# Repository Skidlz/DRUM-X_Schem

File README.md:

# DRUM-X_Schem
Schematics for the Pearl DRUM-X

These schematic are based off of the control section and one voice from the Pearl DRUM-X. 

The board layout is compromised for the sake of the schematic; The SIP resistors have been replace with discrete resistors.

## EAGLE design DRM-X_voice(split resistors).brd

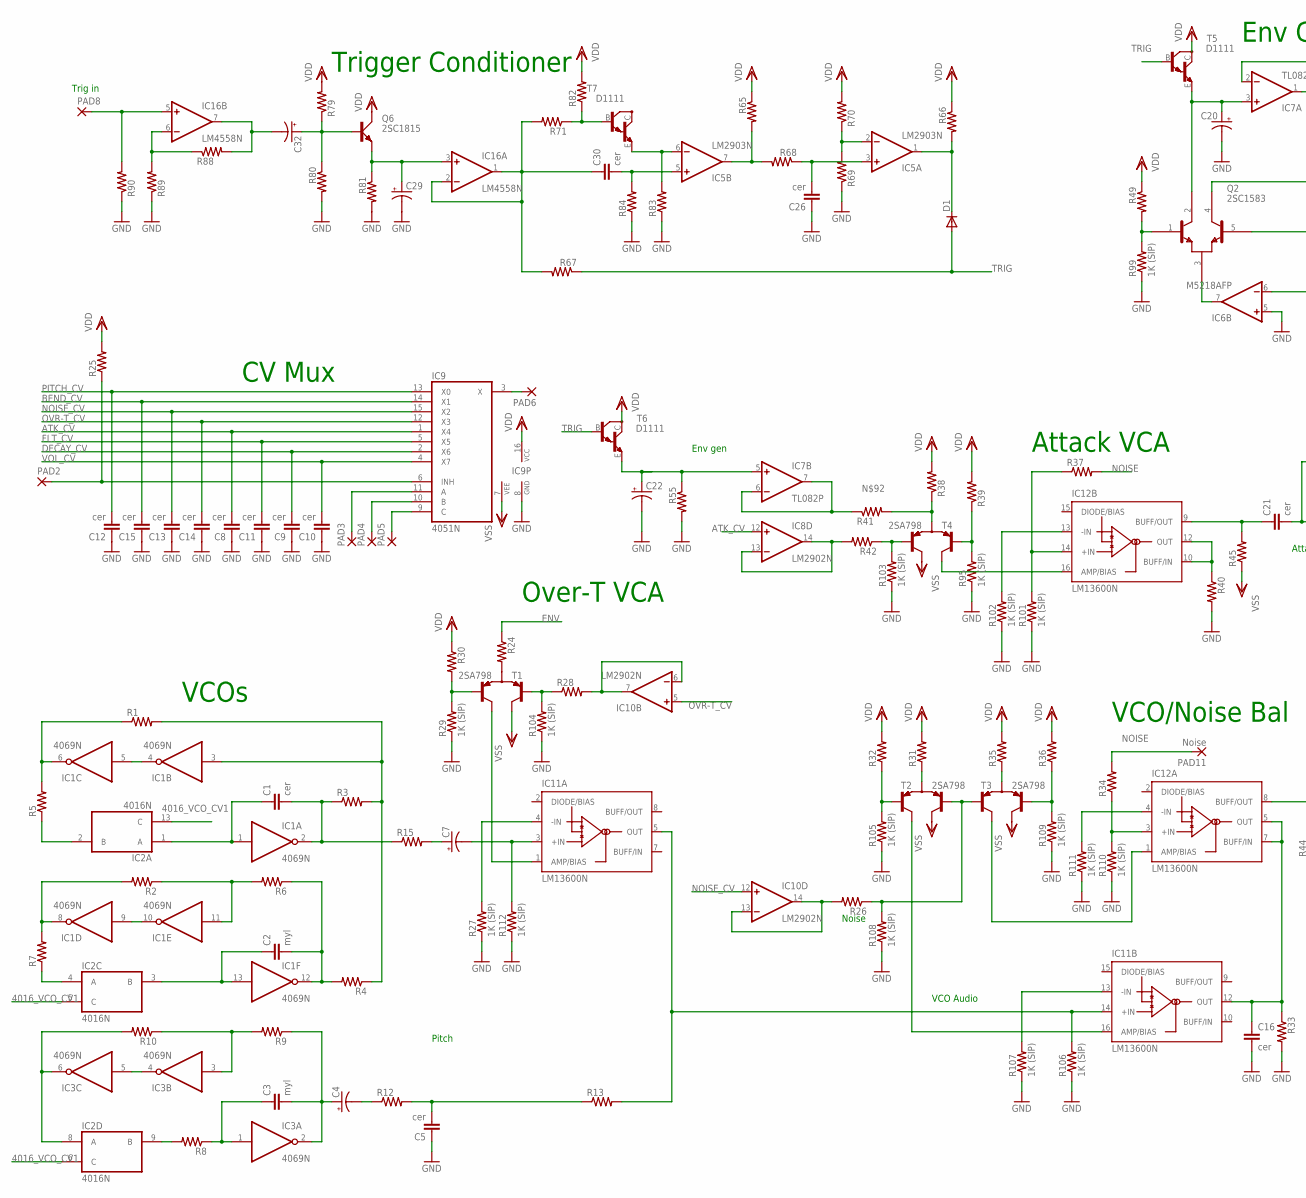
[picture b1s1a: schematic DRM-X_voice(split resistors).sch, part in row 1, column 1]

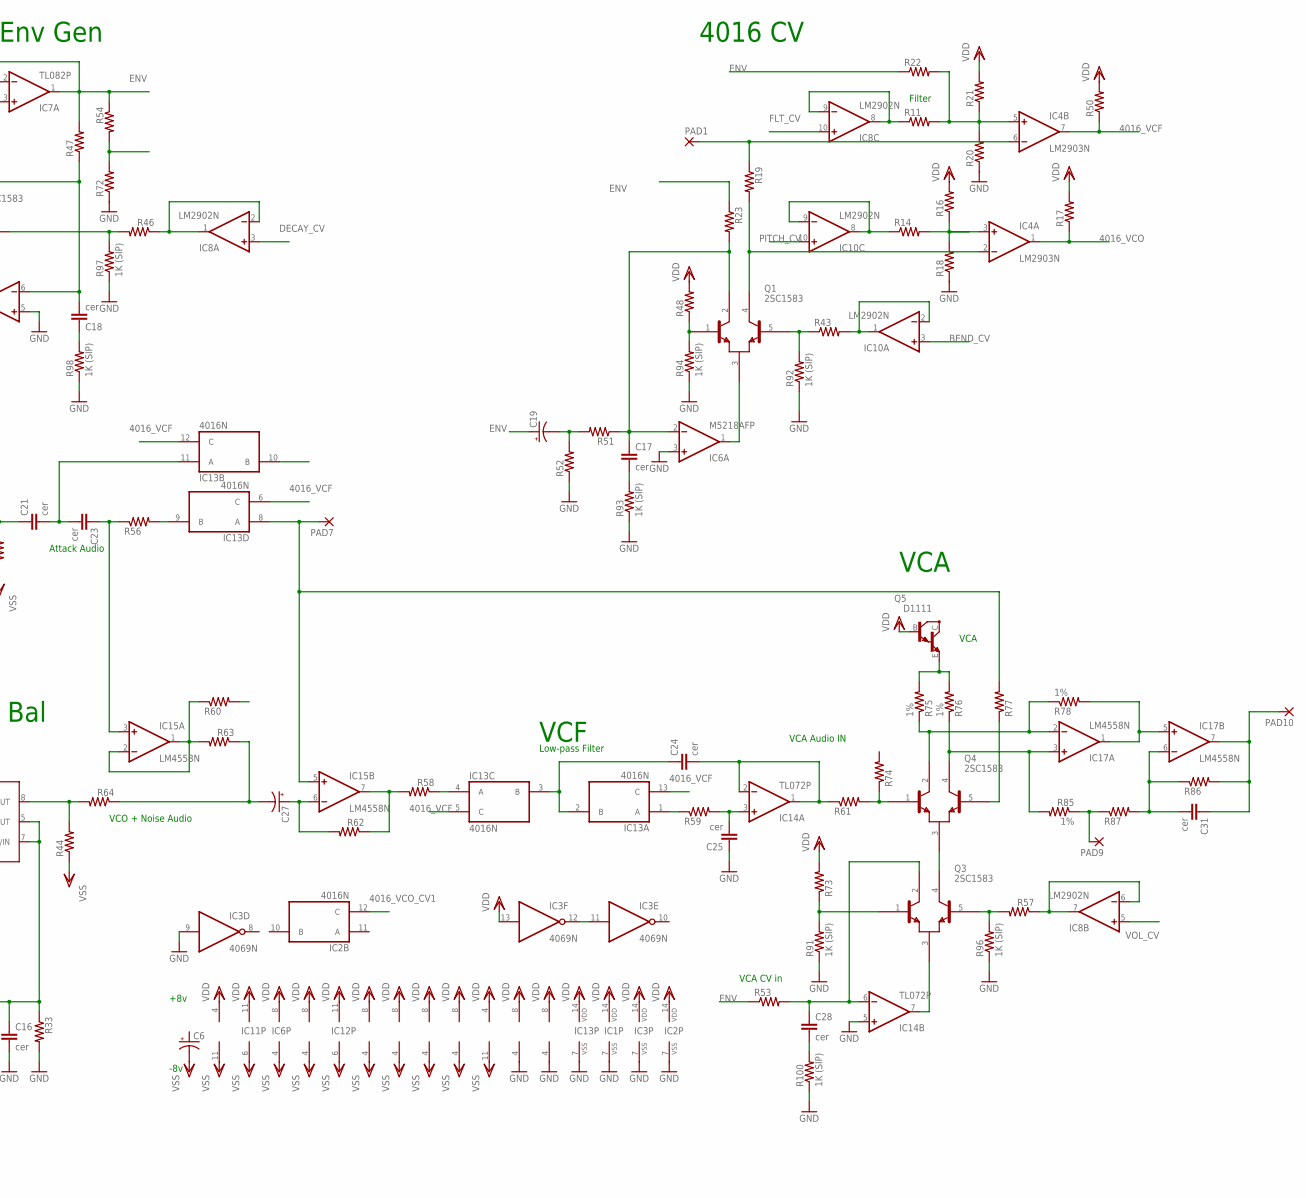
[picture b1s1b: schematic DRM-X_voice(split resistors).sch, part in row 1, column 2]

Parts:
C1, C5, C8, C9, C10, C11, C12, C13, C14, C15, C16, C17, C18, C21, C23, C24, C25, C26, C28, C30, C31: cer; C025-025X050
C2, C3: myl; C025-024X044
C4, C7, C19, C20, C22, C27, C29, C32: CPOL-USE2.5-5; E2,5-5
C6: CPOL-USE2.5-7; E2,5-7
D1: DIODE-D-5; D-5
IC1, IC3: 4069N; DIL14
IC2, IC13: 4016N; DIL14
IC4, IC5: LM2903N; DIL08
IC6: M5218AFP; SOP8
IC7: TL082P; DIL08
IC8, IC10: LM2902N; DIL14
IC9: 4051N; DIL16
IC11, IC12: LM13600N; DIL16
IC14: TL072P; DIL08
IC15, IC16, IC17: LM4558N; DIL08
PAD1, PAD2, PAD3, PAD4, PAD5, PAD6, PAD7, PAD8, PAD9, PAD10: 2,0/0,9-O
PAD11: Noise; 2,0/0,9-O
Q1, Q2, Q3, Q4: 2SC1583; XSIST_SIP5
Q5: D1111; TO92-ECB
Q6: 2SC1815; TO92-LINE
R1, R2, R3, R4, R5, R6, R7, R8, R9, R10, R11, R12, R13, R14, R15, R16, R17, R18, R19, R20, R21, R22, R23, R24, R25, R26, R28, R30, R31, R32, R33, R34, R35, R36, R37, R38, R39, R40, R41, R42, R43, R44, R45, R46, R47, R48, R49, R50, R51, R52, R53, R54, R55, R56, R57, R58, R59, R60, R61, R62, R63, R64, R65, R66, R67, R68, R69, R70, R71, R72, R73, R74, R77, R79, R80, R81, R82, R83, R84, R86, R87, R88, R89, R90: R-US_0204/7; 0204/7
R27, R29, R91, R92, R93, R94, R95, R96, R97, R98, R99, R100, R101, R102, R103, R104, R105, R106, R107, R108, R109, R110, R111, R112: 1K (SIP); 0204/7
R75, R76, R78, R85: 1%; 0204/7
T1, T2, T3, T4: 2SA798; SIP-5
T5, T6, T7: D1111; TO92-ECB

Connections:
4016_VCF: IC4.7 (OUT), IC13.5 (C), IC13.6 (C), IC13.12 (C), IC13.13 (C), R50.1
4016_VCO: IC4.1 (OUT), R17.1
4016_VCO_CV1: IC2.5 (C), IC2.6 (C), IC2.12 (C), IC2.13 (C)
ATK_CV: C8.2, IC8.12 (+IN), IC9.1 (X4)
BEND_CV: C15.2, IC9.14 (X1), IC10.3 (+IN)
DECAY_CV: C9.2, IC8.3 (+IN), IC9.2 (X6)
ENV: C19.+, IC7.1 (OUT), IC7.2 (-IN), R22.1, R23.1, R24.1, R47.2, R53.1, R54.1
FLT_CV: C11.2, IC8.10 (+IN), IC9.5 (X5)
GND: C5.1, C8.1, C9.1, C10.1, C11.1, C12.1, C13.1, C14.1, C15.1, C16.2, C20.-, C22.-, C25.1, C26.1, C29.-, IC1.7 (VSS), IC2.7 (VSS), IC3.7 (VSS), IC3.9 (I), IC4.4 (V-), IC5.4 (V-), IC6.3 (+IN), IC6.5 (+IN), IC9.8 (GND), IC13.7 (VSS), IC14.5 (+IN), R18.1, R20.1, R27.1, R29.1, R33.2, R40.2, R52.1, R55.2, R69.1, R72.1, R80.2, R81.2, R83.1, R84.1, R89.1, R90.1, R91.1, R92.1, R93.1, R94.1, R95.1, R96.1, R97.1, R98.1, R99.1, R100.1, R101.1, R102.1, R103.1, R104.1, R105.1, R106.1, R107.1, R108.1, R109.1, R110.1, R111.1, R112.1
unnamed: IC1.4 (O), IC1.5 (I)
unnamed: IC1.6 (O), R1.1, R5.2
unnamed: C1.1, IC1.1 (I), IC2.1 (A)
unnamed: C1.2, IC1.2 (O), R3.1, R15.1
unnamed: IC1.8 (O), R2.2, R7.2
unnamed: IC1.11 (I), R2.1, R6.2
unnamed: IC1.3 (I), R1.2, R3.2, R4.1
unnamed: IC2.4 (A), R7.1
unnamed: IC1.9 (I), IC1.10 (O)
unnamed: C2.1, IC1.13 (I), IC2.3 (B)
unnamed: C2.2, IC1.12 (O), R4.2, R6.1
unnamed: C3.2, C4.+, IC3.2 (O), R9.1
unnamed: C3.1, IC3.1 (I), R8.1
unnamed: C28.1, IC14.6 (-IN), Q3.2 (C1), R53.2
unnamed: IC3.3 (I), R9.2, R10.1
unnamed: IC2.2 (B), R5.1
unnamed: IC2.8 (A), IC3.6 (O), R10.2
unnamed: IC3.4 (O), IC3.5 (I)
unnamed: IC2.9 (B), R8.2
unnamed: C4.-, R12.1
unnamed: IC3.11 (I), IC3.12 (O)
unnamed: C5.2, R12.2, R13.1
unnamed: IC10.8 (OUT), IC10.9 (-IN), R14.1
unnamed: IC10.6 (-IN), IC10.7 (OUT), R28.2
unnamed: IC10.1 (OUT), IC10.2 (-IN), R43.2
unnamed: IC10.13 (-IN), IC10.14 (OUT), R26.2
unnamed: C21.1, IC12.9 (BUFF/OUT), R45.2
unnamed: IC4.3 (+IN), R14.2, R16.1, R18.2
unnamed: IC8.1 (OUT), IC8.2 (-IN), R46.1
unnamed: IC8.13 (-IN), IC8.14 (OUT), R42.2
unnamed: IC8.8 (OUT), IC8.9 (-IN), R11.1
unnamed: IC8.6 (-IN), IC8.7 (OUT), R57.1
unnamed: IC4.5 (+IN), R11.2, R20.2, R21.1, R22.2
unnamed: C17.1, IC6.2 (-IN), Q1.2 (C1), R23.2, R51.1
unnamed: IC13.4 (A), R58.1
unnamed: IC4.6 (-IN), PAD1.1, R19.1
unnamed: IC4.2 (-IN), Q1.4 (C2), R19.2
unnamed: C7.+, R15.2
unnamed: C7.-, IC11.3 (+IN), R112.2
unnamed: R24.2, T1.3 (E)
unnamed: R28.1, R104.2, T1.1 (B1)
unnamed: R29.2, R30.2, T1.5 (B2)
unnamed: IC6.1 (OUT), Q1.3 (E)
unnamed: IC11.1 (AMP/BIAS), T1.4 (C2)
unnamed: C16.1, IC11.12 (OUT), IC12.5 (OUT), IC12.7 (BUFF/IN), R33.1
unnamed: IC11.4 (-IN), R27.2
unnamed: IC9.6 (INH), PAD2.1, R25.1
unnamed: IC9.9 (C), PAD5.1
unnamed: IC9.10 (B), PAD4.1
unnamed: IC9.11 (A), PAD3.1
unnamed: IC9.3 (X), PAD6.1
unnamed: IC11.13 (-IN), R107.2
unnamed: R32.1, R105.2, T2.1 (B1)
unnamed: R26.1, R108.2, T2.5 (B2), T3.1 (B1)
unnamed: R31.1, T2.3 (E)
unnamed: IC11.16 (AMP/BIAS), T2.2 (C1)
unnamed: IC12.3 (+IN), R34.1, R110.2
unnamed: IC12.1 (AMP/BIAS), T3.2 (C1)
unnamed: R36.1, R109.2, T3.5 (B2)
unnamed: R35.1, T3.3 (E)
unnamed: R39.1, R95.2, T4.1 (B1)
unnamed: IC12.8 (BUFF/OUT), R44.2, R64.2
unnamed: IC12.4 (-IN), R111.2
unnamed: IC13.9 (B), R56.2
unnamed: R38.1, R41.2, T4.3 (E)
unnamed: IC12.16 (AMP/BIAS), T4.2 (C1)
unnamed: IC12.14 (+IN), R37.1, R101.2
unnamed: IC12.13 (-IN), R102.2
unnamed: R42.1, R103.2, T4.5 (B2)
unnamed: IC12.10 (BUFF/IN), IC12.12 (OUT), R40.1
unnamed: Q1.5 (B2), R43.1, R92.2
unnamed: C17.2, R93.2
unnamed: Q2.5 (B2), R46.2, R97.2
unnamed: Q1.1 (B1), R48.1, R94.2
unnamed: C18.2, IC6.6 (-IN), Q2.4 (C2), R47.1
unnamed: C18.1, R98.2
unnamed: Q2.1 (B1), R49.2, R99.2
unnamed: IC6.7 (OUT), Q2.3 (E)
unnamed: C24.1, IC13.2 (B), IC13.3 (B)
unnamed: Q3.1 (B1), R73.1, R91.2
unnamed: C21.2, C23.2, IC13.11 (A)
unnamed: C19.-, R51.2, R52.2
unnamed: C20.+, IC7.3 (+IN), Q2.2 (C1), T5.E
unnamed: IC7.6 (-IN), IC7.7 (OUT), R41.1
unnamed: C23.1, IC15.3 (+IN), R56.1
unnamed: C22.+, IC7.5 (+IN), R55.1, T6.E
unnamed: IC13.1 (A), R59.1
unnamed: C25.2, IC14.3 (+IN), R59.2
unnamed: C24.2, IC14.1 (OUT), IC14.2 (-IN), R61.1
unnamed: IC15.1 (OUT), IC15.2 (-IN), R60.1, R63.2
unnamed: IC15.7 (OUT), R58.2, R62.1
unnamed: C27.+, IC15.6 (-IN), R62.2
unnamed: D1.C, IC5.1 (OUT), R66.2
unnamed: IC13.8 (A), IC15.5 (+IN), PAD7.1, R77.2
unnamed: IC5.7 (OUT), R65.2, R68.2
unnamed: IC5.2 (-IN), R69.2, R70.1
unnamed: PAD9.1, R85.1, R87.1
unnamed: R54.2, R72.2
unnamed: C26.2, IC5.3 (+IN), R68.1
unnamed: C27.-, R63.1, R64.1
unnamed: C28.2, R100.2
unnamed: Q3.4 (C2), Q4.3 (E)
unnamed: Q4.1 (B1), R61.2, R74.1
unnamed: C29.+, IC16.3 (+IN), Q6.3 (E), R81.1
unnamed: IC17.3 (+IN), Q4.4 (C2), R76.1, R85.2
unnamed: Q4.5 (B2), R77.1
unnamed: IC17.2 (-IN), Q4.2 (C1), R75.1, R78.1
unnamed: Q5.E, R75.2, R76.2
unnamed: IC17.1 (OUT), IC17.5 (+IN), R78.2
unnamed: C32.+, Q6.1 (B), R79.1, R80.1
unnamed: IC16.6 (-IN), R88.1, R89.2
unnamed: C30.1, IC16.1 (OUT), IC16.2 (-IN), R67.2, R71.2
unnamed: R71.1, R82.1, T7.B
unnamed: IC5.6 (-IN), R83.2, T7.E
unnamed: C30.2, IC5.5 (+IN), R84.2
unnamed: C32.-, IC16.7 (OUT), R88.2
unnamed: IC14.7 (OUT), Q3.3 (E)
unnamed: Q3.5 (B2), R57.2, R96.2
unnamed: IC16.5 (+IN), PAD8.1, R90.2
unnamed: C31.2, IC17.6 (-IN), R86.1, R87.2
unnamed: C31.1, IC17.7 (OUT), PAD10.1, R86.2
NOISE: PAD11.1, R34.2, R37.2
NOISE_CV: C13.2, IC9.15 (X2), IC10.12 (+IN)
OVR-T_CV: C14.2, IC9.12 (X3), IC10.5 (+IN)
PITCH_CV: C12.2, IC9.13 (X0), IC10.10 (+IN)
TRIG: D1.A, R67.1, T5.B, T6.B
VCO_OUT: IC11.5 (OUT), IC11.14 (+IN), R13.2, R106.2
VDD: IC1.14 (VDD), IC2.14 (VDD), IC3.13 (I), IC3.14 (VDD), IC4.8 (V+), IC5.8 (V+), IC6.8 (V+), IC7.8 (V+), IC8.4 (V+), IC9.16 (VCC), IC10.4 (V+), IC11.11 (V+), IC12.11 (V+), IC13.14 (VDD), IC14.8 (V+), IC15.8 (V+), IC16.8 (V+), IC17.8 (V+), Q5.B, Q6.2 (C), R16.2, R17.2, R21.2, R25.2, R30.1, R31.2, R32.2, R35.2, R36.2, R38.2, R39.2, R48.2, R49.1, R50.2, R65.1, R66.1, R70.2, R73.2, R79.2, R82.2, T5.C, T6.C
VOL_CV: C10.2, IC8.5 (+IN), IC9.4 (X7)
VSS: C6.-, IC6.4 (V-), IC7.4 (V-), IC8.11 (V-), IC9.7 (VEE), IC10.11 (V-), IC11.6 (V-), IC12.6 (V-), IC14.4 (V-), IC15.4 (V-), IC16.4 (V-), IC17.4 (V-), R44.1, R45.1, T1.2 (C1), T2.4 (C2), T3.4 (C2), T4.4 (C2)

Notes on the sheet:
Filter
Noise
Pitch
Trig in
VCA
VCA CV in
VCA Audio IN
VCO Audio
VCO + Noise Audio
Attack Audio
Low-pass Filter
Env gen
Env Gen
4016 CV
VCF
VCO/Noise Bal
Attack VCA
CV Mux
VCOs
Over-T VCA
+8v
-8v
Trigger Conditioner

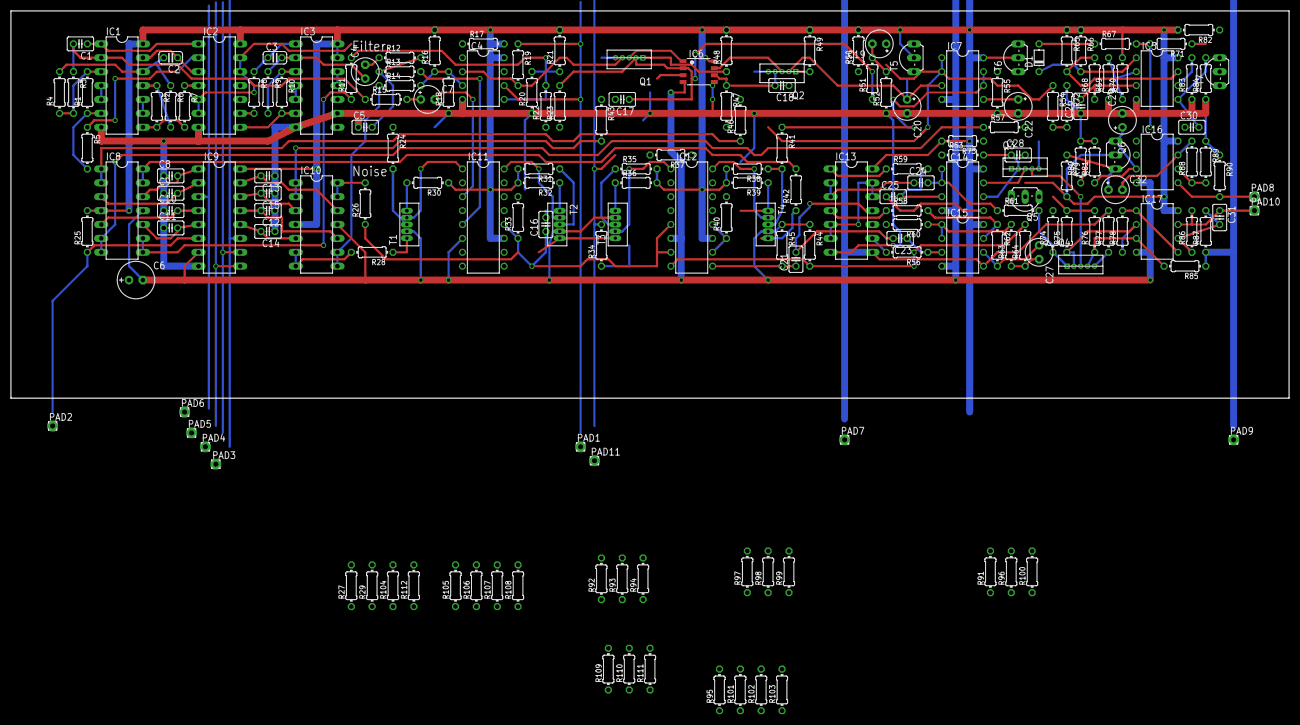
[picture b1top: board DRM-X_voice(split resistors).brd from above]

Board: 2 copper layers, 233.7 x 70.8 mm, 186 parts (0 on the bottom side), 139 nets.

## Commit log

2017-09-23 Added Files
2017-11-11 Added digital control schematic
